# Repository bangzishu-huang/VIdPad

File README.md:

# VidPad
A macropad created for more efficient video viewing. There are 6 keys which are lit with LEDs, a rotary encoder for volume control, an OLED screen, and a XIAO RP2040 (microcontroller). 

This roughly took me around 18+ hours because it was my first time designing any type of hardware, but I really enjoyed the process!

(Will add demo images and videos once VidPad is fully assembled)

# PCB
Everything was done on KiCAD, and I used a JLCPCB plugin for exporting the gerber files.

- Schematic
- 

- PCB without Zones
- 

- PCB with Zones
- 

# Case
The case was made in AutoDesk Inventor due to my prior knowledge in the software. The PCB is held together through a sandwich mount.

- Top
- 

- Middle
- 

- Bottom
- 

# Firmware
VidPad uses QMK for firmware
- VIA supported
- Rotary encoder for volume control
- OLED displaying bongo cat!
- 6 keys for effecient video viewing
- RGB lighting

# BOM (Bill of Materials)
- 1x Seeed XIAO RP2040
- 6x 1N4148 Diodes
- 6x MX-Style switches
- 6x white blank DSA keycaps
- 6x SK6812 MINI-E LEDs
- 1x EC11 Rotary encoder
- 1x 0.91 inch OLED display
- 4x M3x16mm screws

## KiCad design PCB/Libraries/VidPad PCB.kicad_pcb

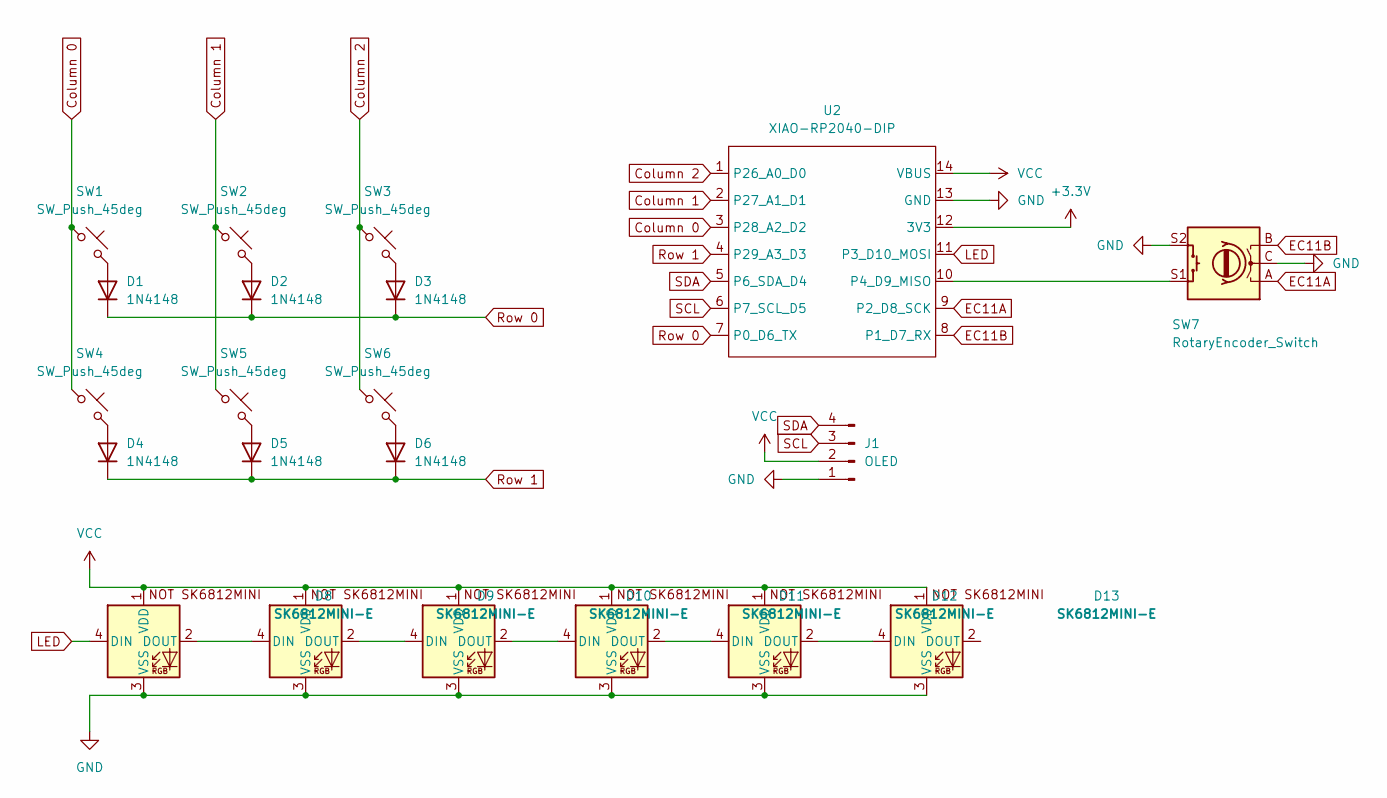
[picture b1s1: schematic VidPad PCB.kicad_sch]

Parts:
D1, D2, D3, D4, D5, D6: 1N4148; D_DO-35_SOD27_P7.62mm_Horizontal
D8, D9, D10, D11, D12, D13: SK6812MINI-E; SK6812MINI-E_fixed
J1: OLED; SSD1306-0.91-OLED-4pin-128x32
SW1, SW2, SW3, SW4, SW5, SW6: SW_Push_45deg; SW_Cherry_MX_1.00u_PCB
SW7: RotaryEncoder_Switch; RotaryEncoder_Alps_EC11E-Switch_Vertical_H20mm
U2: XIAO-RP2040-DIP

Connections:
+3.3V: U2.12 (3V3)
Column 0: SW1.1, SW4.1, U2.3 (P28_A2_D2)
Column 1: SW2.1, SW5.1, U2.2 (P27_A1_D1)
Column 2: SW3.1, SW6.1, U2.1 (P26_A0_D0)
EC11A: SW7.A, U2.9 (P2_D8_SCK)
EC11B: SW7.B, U2.8 (P1_D7_RX)
GND: D8.3 (VSS), D9.3 (VSS), D10.3 (VSS), D11.3 (VSS), D12.3 (VSS), D13.3 (VSS), J1.1, SW7.C, SW7.S2, U2.13 (GND)
LED: D8.4 (DIN), U2.11 (P3_D10_MOSI)
unnamed: D1.2 (A), SW1.2
unnamed: D2.2 (A), SW2.2
unnamed: D3.2 (A), SW3.2
unnamed: D4.2 (A), SW4.2
unnamed: D5.2 (A), SW5.2
unnamed: D6.2 (A), SW6.2
unnamed: D8.2 (DOUT), D9.4 (DIN)
unnamed: D9.2 (DOUT), D10.4 (DIN)
unnamed: D10.2 (DOUT), D11.4 (DIN)
unnamed: D11.2 (DOUT), D12.4 (DIN)
unnamed: D12.2 (DOUT), D13.4 (DIN)
unnamed: SW7.S1, U2.10 (P4_D9_MISO)
Row 0: D1.1 (K), D2.1 (K), D3.1 (K), U2.7 (P0_D6_TX)
Row 1: D4.1 (K), D5.1 (K), D6.1 (K), U2.4 (P29_A3_D3)
SCL: J1.3, U2.6 (P7_SCL_D5)
SDA: J1.4, U2.5 (P6_SDA_D4)
VCC: D8.1 (VDD), D9.1 (VDD), D10.1 (VDD), D11.1 (VDD), D12.1 (VDD), D13.1 (VDD), J1.2, U2.14 (VBUS)

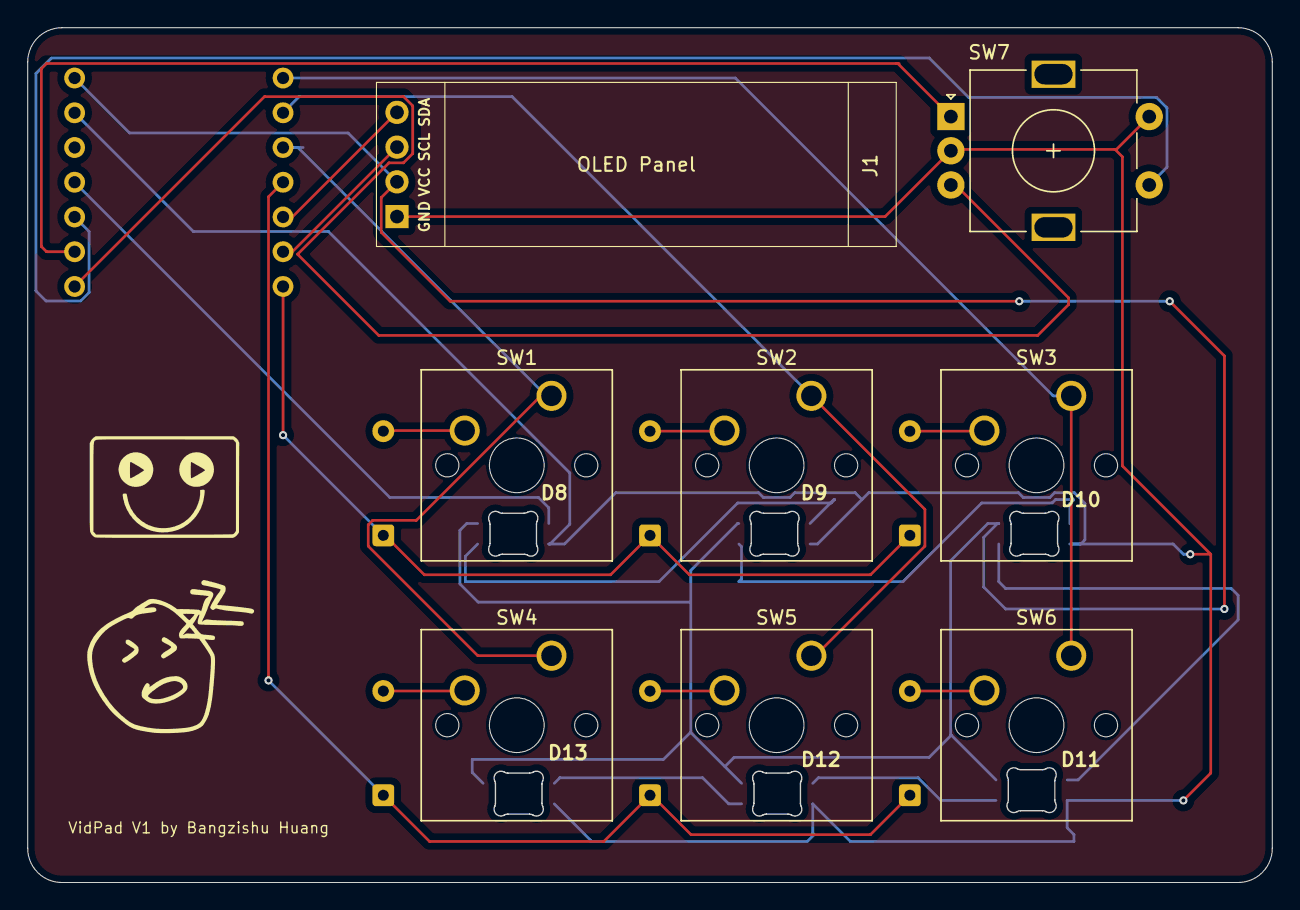
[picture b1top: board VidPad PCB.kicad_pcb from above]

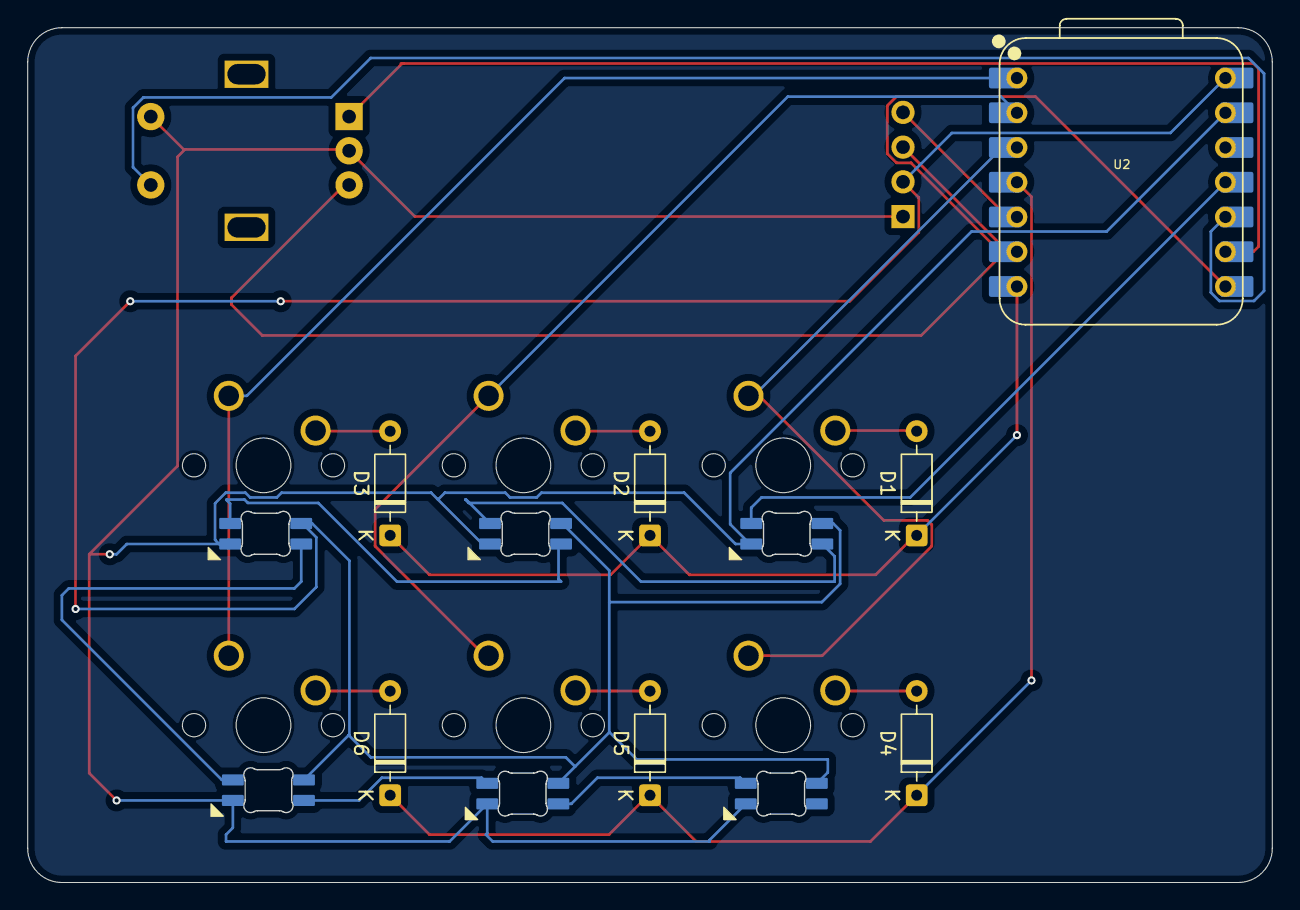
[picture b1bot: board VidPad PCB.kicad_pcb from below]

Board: 2 copper layers, 91.0 x 62.5 mm, 22 parts (7 on the bottom side), 24 nets.

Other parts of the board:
VidPad V1 by Bangzishu Huang: LOGO

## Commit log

2026-02-15 Added library for pcb
    Added PCB schematic and design libraries
2026-02-15 Added to PCB folder
2026-02-15 Adding some folders
2026-02-16 Added CAD files and ss
2026-02-16 Organizing
2026-02-17 added firmware
2026-02-17 updating production and firmware
2026-02-17 added gerber
2026-02-18 Fix typo in project name from 'VIdPad' to 'VidPad'
2026-02-18 Expand README with PCB, case, firmware, and BOM details
    Added detailed sections about PCB design, case construction, firmware features, and BOM.
2026-02-18 Added ss of case
2026-02-18 Replace old screenshot with new image
    Updated the image in the README to a new screenshot.
2026-02-18 added updated cad files and organized folders
2026-02-18 organized folders for better viewing
2026-03-05 Add SK6812 MINI-E LEDs to component list
